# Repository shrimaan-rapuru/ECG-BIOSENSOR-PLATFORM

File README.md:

# Development and Evaluation of a Low-Cost Real-Time ECG Biosensing Platform

> Integrating Signal Processing, Robustness Analysis, and Physiological Visualization

**Shrimaan Rapuru** | The Early College at Guilford | Summer 2026
[Technical Report](report/) | [Results](results/) | [Dashboard](dashboard/)

---

## Abstract

This project investigates whether consumer-grade biosensing hardware can produce
physiologically meaningful cardiac metrics through optimized signal processing,
motivated by observed healthcare access inequality at Open Door Ministries, a
homeless shelter where I volunteer. Using a SparkFun AD8232 ECG module and Arduino
Uno R4 Minima ($102 total), I designed and validated a complete real-time ECG
acquisition and analysis pipeline. A 4th-order Butterworth bandpass filter
(0.5-40Hz) with IIR notch (60Hz) achieved visible PQRST morphology and 96.3%
mean R-peak detection accuracy across five validated resting trials. Three
structured experiments evaluated physiological response (resting vs. exercise vs.
recovery), electrode placement robustness, and comparative filter algorithm
performance. A key finding: Moving Average filtering achieves higher SNR but lower
detection reliability than Butterworth filtering, revealing that SNR alone is
insufficient to evaluate ECG filter quality. Results suggest low-cost ECG
acquisition is viable with careful signal processing methodology.

---

## Hero Figure

*Real-time ECG signal captured at 533Hz. All 5 PQRST waves clearly identified.
BPM: 89.5 | SDNN: 17.63ms | RMSSD: 23.65ms | 42 peaks detected.*

---

## Why This Matters

Standard clinical ECG systems cost $1,000-$10,000, placing cardiac monitoring
out of reach for many individuals and resource-limited settings. This project
asks a practical engineering question: can a $102 consumer-grade system produce
physiologically meaningful cardiac metrics with careful signal processing?

The answer, supported by validated experiments, is yes. This work demonstrates
that accessibility and rigor are not mutually exclusive. The same engineering
discipline that produces expensive medical devices can be applied to low-cost
hardware to yield credible, reproducible physiological measurements.

This project was motivated by direct observation of healthcare access inequality
at Open Door Ministries, where I coordinate volunteer scheduling. Every system
I build asks the same question I first asked there: how do we build tools that
actually reach the people who need them most?

---

## Key Results

- 96.3% mean R-peak detection accuracy across 5 validated resting trials
- 20% post-exercise BPM elevation (90 to 108 BPM) with parasympathetic rebound confirmed
- All 5 PQRST waves visible: Q-wave 7.9% of R, S-wave 28.0% of R
- Single electrode displacement (+-2cm) has minimal BPM impact; combined displacement degrades accuracy 6.3%
- Moving Average achieves higher SNR but lower detection reliability than Butterworth -- confirming SNR alone is insufficient to evaluate ECG filter quality

---

## System Architecture

| Layer | Components |
|---|---|
| Hardware | AD8232 AFE -> Arduino R4 Minima (14-bit ADC, 533Hz) -> USB Serial |
| Signal Processing | Butterworth Bandpass (0.5-40Hz) + IIR Notch (60Hz) + Peak Detection |
| Analysis | BPM calculation, HRV (SDNN/RMSSD), PQRST morphology |
| Visualization | Streamlit live dashboard + Matplotlib experimental plots |

---

## Hardware

### Bill of Materials

| Component | Part Number | Cost | Purpose |
|---|---|---|---|
| SparkFun AD8232 | SEN-12650 | $24.41 | ECG analog front-end |
| Electrode Cable | CAB-12970 | $9.60 | 3-lead electrode connection |
| Arduino Uno R4 Minima | -- | $19.99 | 14-bit ADC + USB serial |
| Ag/AgCl Electrodes 100pk | Kendall | $15.30 | Skin contact |
| Breadboard + jumpers | -- | $8.99 | Prototyping |
| Alcohol prep pads | -- | $7.00 | Skin preparation |
| Header pins | HiLetgo 40-pin | $5.49 | AD8232 connection |
| **Total** | | **$90.78** | |

### Wiring

| AD8232 Pin | Arduino Pin | Function |
|---|---|---|
| 3.3V | 3.3V | Power |
| GND | GND | Ground |
| OUTPUT | A0 | ECG signal |
| LO+ | D10 | Lead-off detect + |
| LO- | D11 | Lead-off detect - |

### Hardware Photos

| | |
|---|---|
|  |  |
| Hardware setup — AD8232 + Arduino R4 Minima | Electrode placement on subject |
|  |  |
| Apple Watch BPM validation — simultaneous recording | Full system setup overview |
### Electrode Placement
- **Red** -> Right chest (below collarbone)
- **Blue** -> Left chest (below collarbone)
- **Black** -> Right lower abdomen (ground)

### PCB Design
Custom PCB designed in EasyEDA featuring AD8232, decoupling capacitors (2x100nF,
1x10uF), bias resistors (2x10kOhm), 3.5mm PJ-320A electrode jack, and Arduino
pin headers. All components selected from JLCPCB assembly library.
Fabrication via JLCPCB planned as Phase 2.

---

## Signal Processing Pipeline

### Filter Specifications

| Filter | Type | Cutoff | Order | Purpose |
|---|---|---|---|---|
| High-pass | Butterworth | 0.5 Hz | 4 | Baseline drift removal |
| Low-pass | Butterworth | 40 Hz | 4 | EMG artifact removal |
| Notch | IIR | 60 Hz | Q=30 | Powerline interference |

**Implementation:** Zero-phase filtering (scipy filtfilt) eliminates phase
distortion for accurate RR interval timing. Critical for HRV analysis where
millisecond-level timing precision determines metric validity.

**Design decision:** The 0.5 Hz lower cutoff was deliberately calibrated to
preserve the low-amplitude P-wave rather than aggressively filtering baseline
drift -- prioritizing physiological completeness over visual cleanliness.

### Sampling Architecture

| Parameter | Value |
|---|---|
| Sampling frequency | 533.3 Hz (validated -- not assumed) |
| ADC resolution | 14-bit |
| Serial baud rate | 115200 bps |
| Timing jitter | 3.61ms |
| Recording duration | 30 seconds (16,000 samples) |
| Signal inversion | Applied (electrode polarity correction) |

### Peak Detection

Adaptive threshold: median + 0.5 x std
Minimum R-R distance: 0.6 x fs (prevents double detection)
Mean accuracy: 96.3% (range: 89.4%-100.0%, N=5 trials)

### Key Signal Processing Insight

A critical finding from Experiment 3: Moving Average filtering achieved higher
mean SNR (0.63 +/- 1.99 dB) compared to Butterworth bandpass (-10.14 +/- 3.58 dB),
yet demonstrated inferior BPM consistency across trials.

This reveals a fundamental limitation of SNR as an ECG filter evaluation metric:
- Moving Average smooths broadband noise but distorts QRS morphology
- Butterworth bandpass selectively removes non-physiological frequency content
- Visually cleaner signals are not necessarily physiologically superior
- Morphology preservation matters more than signal power ratio for reliable detection

### PQRST Morphology

| Wave | Amplitude | % of R | Physiological Meaning |
|---|---|---|---|
| P | visible | -- | Atrial depolarization |
| Q | -18.0 ADC | 7.9% | Septal depolarization |
| R | 228.3 ADC | 100% | Ventricular depolarization |
| S | -64.0 ADC | 28.0% | Late ventricular depolarization |
| T | ~50 ADC | ~22% | Ventricular repolarization |

---

## Experiments

### Experiment 1 -- Resting vs Exercise vs Recovery

| State | BPM | SDNN | RMSSD |
|---|---|---|---|
| Resting avg | 91.0 | 41.31ms | 45.93ms |
| Pre-exercise | 90 | -- | -- |
| Post-exercise | 108 | -- | -- |
| Recovery 1 | 86.7 | 54.33ms | 45.45ms |
| Recovery 2 | 92.1 | 20.18ms | 9.91ms |
| Recovery 3 | 95.7 | 9.24ms | 9.42ms |

### Experiment 2 -- Electrode Placement Robustness

| Condition | Avg BPM | vs Standard |
|---|---|---|
| Standard | 82.2 | baseline |
| RA off 2cm | 81.6 | -0.7% |
| LA off 2cm | 83.0 | +1.0% |
| Both off 2cm | 87.4 | +6.3% |

### Experiment 3 -- Filter Algorithm Comparison

| Algorithm | SNR | BPM | Time |
|---|---|---|---|
| Moving Average | 0.63 +/- 1.99 dB | 88.02 +/- 8.08 | 0.69ms |
| Butterworth | -10.14 +/- 3.58 dB | 80.14 +/- 22.04 | 4.4ms |
| Butterworth+Notch | -10.16 +/- 3.58 dB | 79.7 +/- 22.92 | 2.11ms |

---

## Live Dashboard

**Features:**
- Real-time ECG waveform with R-peak markers
- Live BPM display (color-coded red if >100 BPM)
- SDNN and RMSSD updating in real time
- Raw vs filtered signal toggle
- Lead-off detection alert
- CSV export for offline analysis

**Run locally:**

```
cd dashboard
pip install -r requirements.txt
streamlit run ecg_dashboard.py
```

> Not a medical device. For educational and research purposes only.

---

## Installation

```
pip install streamlit pandas numpy scipy pyserial plotly matplotlib
```

Arduino setup: Install Arduino IDE 2.x, select Arduino UNO R4 Minima,
set baud rate 115200, close Serial Monitor before running Python scripts.

---

## Repository Structure

```
ecg-biosensor/
├── signal_processing/           # Python analysis scripts
│   ├── serial_reader.py         # Arduino serial data capture
│   ├── filters.py               # Butterworth + notch filter pipeline
│   ├── peak_detection.py        # R-peak detection + HRV analysis
│   ├── pqrst_analysis.py        # PQRST wave visualization
│   ├── raw_vs_filtered.py       # Normalized comparison plots
│   ├── negative_deflection.py   # Q/S wave investigation
│   ├── filter_visual_comparison.py  # 4-panel algorithm comparison
│   ├── experiment_3.py          # Algorithm benchmarking
│   ├── quick_bpm_check.py       # 10-second live BPM check
│   └── validation.py            # Peak accuracy validation
├── dashboard/                   # Streamlit live dashboard
│   ├── ecg_dashboard.py
│   └── requirements.txt
├── results/                     # All experimental data and plots
│   ├── experiment_1/            # Resting/exercise/recovery (10 trials)
│   ├── experiment_2/            # Electrode placement (12 trials)
│   └── experiment_3/            # Filter comparison (15 trials)
├── hardware/                    # PCB design and documentation
│   ├── ecg_schematic.png
│   ├── block_diagram.png
│   └── dashboard_screenshots/
└── report/                      # Technical report and references
    └── references/              # 5 peer-reviewed papers
```

---

## Limitations

- **Single subject:** All data from one subject -- findings cannot be generalized
- **Short HRV windows:** 30-second recordings below the 5-minute clinical standard
- **Motion artifact:** Post-exercise filtered-pipeline recordings were unreliable
- **SNR methodology:** Standard SNR penalizes DC attenuation -- may not reflect morphology quality
- **Breadboard connections:** Mechanical instability motivates PCB fabrication

---

## Future Work

- [ ] Custom PCB fabrication via JLCPCB (schematic complete)
- [ ] Multi-subject validation study (N>=10)
- [ ] Streamlit Cloud deployment
- [ ] 5-minute HRV recording windows
- [ ] lfilter for real-time causal filtering
- [ ] Bland-Altman analysis vs commercial pulse oximeter
- [ ] Journal of Student Research submission (August 2026)

---

## References

1. Pan, J. & Tompkins, W.J. (1985). A real-time QRS detection algorithm. IEEE Trans Biomed Eng, 32(3), 230-236.
2. Task Force of ESC & NASPE (1996). Heart rate variability standards. Circulation, 93(5), 1043-1065.
3. Serhani, M.A. et al. (2020). ECG monitoring systems review. Sensors, 20(6), 1796.
4. Kohler, B.U. et al. (2002). Software QRS detection principles. IEEE Eng Med Biol, 21(1), 42-57.
5. Christov, I.I. (2004). Real time QRS detection adaptive threshold. BioMed Eng OnLine, 3(1), 28.

---

## License

MIT License -- see LICENSE for details.

---

## About

This project was motivated by observations at Open Door Ministries, a homeless
shelter where I volunteer as scheduling coordinator. Witnessing healthcare access
inequality firsthand raised a question that drove this research: can low-cost
consumer hardware produce clinically meaningful cardiac metrics with careful
signal processing? The answer, supported by validated experiments, is yes.

> "Every project I pursue asks the same question I first asked at Open Door:
> how do we build systems that actually reach the people who need them most?"

Shrimaan Rapuru | The Early College at Guilford, NC

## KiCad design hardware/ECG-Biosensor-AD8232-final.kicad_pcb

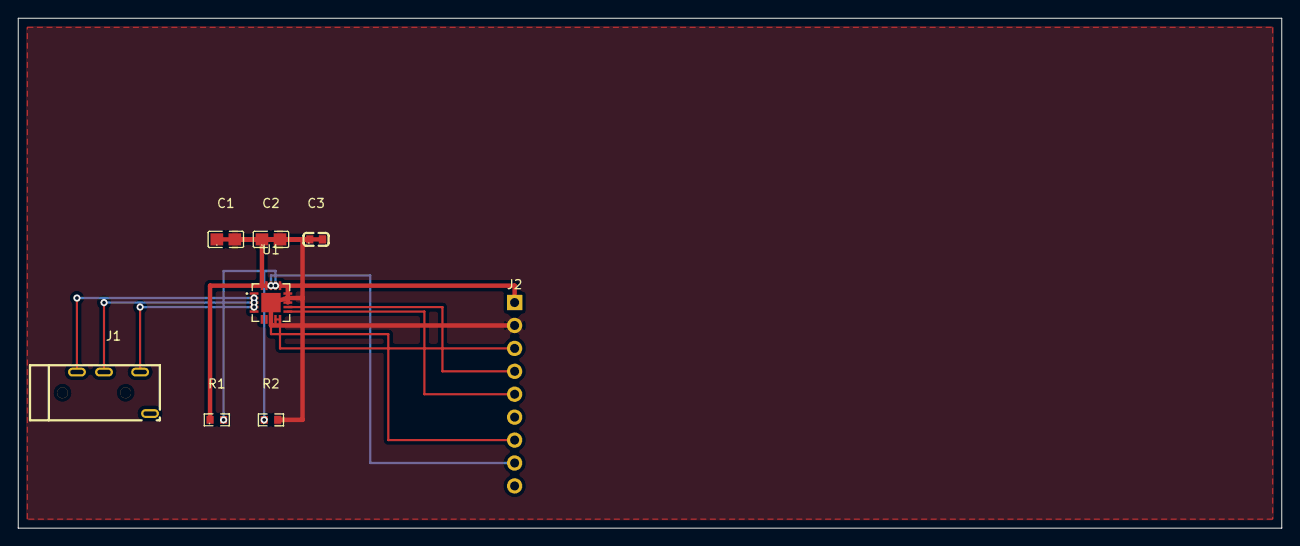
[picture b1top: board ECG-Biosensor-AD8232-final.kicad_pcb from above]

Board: 2 copper layers, 140.0 x 56.5 mm, 8 parts (0 on the bottom side), 11 nets.

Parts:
C1, C2: 100nF; C0805
C3: 10uF; C0603
J1: PJ-320A; AUDIO-TH_PJ-320A_C49284721
J2: OUTPUT_HDR; HDR-TH_9P-P2.54-V
R1, R2: 10k; R0603
U1: AD8232ACPZ-R7; LFCSP-20_L4.0-W4.0-P0.50-TL-EP2.7

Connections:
ECG_INN: J1.3, U1.3
ECG_INP: J1.5, U1.2
ECG_OUT: J2.3, U1.10
GND: C1.2, C2.2, C3.2, J2.2, R2.2, U1.14, U1.21
IAOUT: J2.8, U1.18
LO_MINUS: J2.5, U1.11
LO_PLUS: J2.4, U1.12
REFIN: R1.2, R2.1, U1.17
REFOUT: J2.7, U1.8
RLD: J1.4, U1.4, U1.5
VCC: C1.1, C2.1, C3.1, J2.1, J2.6, R1.1, U1.13, U1.16, U1.20

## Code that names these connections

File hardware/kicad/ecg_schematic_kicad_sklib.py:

from collections import defaultdict
from skidl import Pin, Part, Alias, SchLib, SKIDL, TEMPLATE

from skidl.pin import pin_types

SKIDL_lib_version = '0.0.1'

ecg_schematic_kicad = SchLib(tool=SKIDL).add_parts(*[
        Part(**{ 'name':'C', 'dest':TEMPLATE, 'tool':SKIDL, 'aliases':Alias({'C'}), 'ref_prefix':'C', 'fplist':None, 'footprint':'ecg_kicad:C0805', 'keywords':None, 'description':'', 'datasheet':None, 'pins':[
            Pin(num='1',name='P',func=pin_types.PASSIVE),
            Pin(num='2',name='N',func=pin_types.PASSIVE)] }),
        Part(**{ 'name':'R', 'dest':TEMPLATE, 'tool':SKIDL, 'aliases':Alias({'R'}), 'ref_prefix':'R', 'fplist':None, 'footprint':'ecg_kicad:R0603', 'keywords':None, 'description':'', 'datasheet':None, 'pins':[
            Pin(num='1',name='P',func=pin_types.PASSIVE),
            Pin(num='2',name='N',func=pin_types.PASSIVE)] }),
        Part(**{ 'name':'PJ320A', 'dest':TEMPLATE, 'tool':SKIDL, 'aliases':Alias({'PJ320A'}), 'ref_prefix':'J', 'fplist':None, 'footprint':'ecg_kicad:AUDIO-TH_PJ-320A_C49284721', 'keywords':None, 'description':'', 'datasheet':None, 'pins':[
            Pin(num='1',name='T',func=pin_types.PASSIVE),
            Pin(num='2',name='R1',func=pin_types.PASSIVE),
            Pin(num='3',name='S',func=pin_types.PASSIVE)] }),
        Part(**{ 'name':'Conn1x9', 'dest':TEMPLATE, 'tool':SKIDL, 'aliases':Alias({'Conn1x9'}), 'ref_prefix':'J', 'fplist':None, 'footprint':'ecg_kicad:HDR-TH_40P-P2.54-V-M-1', 'keywords':None, 'description':'', 'datasheet':None, 'pins':[
            Pin(num='1',name='P1',func=pin_types.PASSIVE),
            Pin(num='2',name='P2',func=pin_types.PASSIVE),
            Pin(num='3',name='P3',func=pin_types.PASSIVE),
            Pin(num='4',name='P4',func=pin_types.PASSIVE),
            Pin(num='5',name='P5',func=pin_types.PASSIVE),
            Pin(num='6',name='P6',func=pin_types.PASSIVE),
            Pin(num='7',name='P7',func=pin_types.PASSIVE),
            Pin(num='8',name='P8',func=pin_types.PASSIVE),
            Pin(num='9',name='P9',func=pin_types.PASSIVE)] }),
        Part(**{ 'name':'AD8232ACPZ-R7', 'dest':TEMPLATE, 'tool':SKIDL, 'aliases':Alias({'AD8232ACPZ-R7'}), 'ref_prefix':'U', 'fplist':None, 'footprint':'ecg_kicad:LFCSP-20_L4.0-W4.0-P0.50-TL-EP2.7', 'keywords':None, 'description':'', 'datasheet':None, 'pins':[
            Pin(num='1',name='HPDRIVE',func=pin_types.BIDIR),
            Pin(num='2',name='+IN',func=pin_types.INPUT),
            Pin(num='3',name='-IN',func=pin_types.INPUT),
            Pin(num='4',name='RLDFB',func=pin_types.INPUT),
            Pin(num='5',name='RLD',func=pin_types.OUTPUT),
            Pin(num='6',name='SW',func=pin_types.BIDIR),
            Pin(num='7',name='OPAMP+',func=pin_types.INPUT),
            Pin(num='8',name='REFOUT',func=pin_types.OUTPUT),
            Pin(num='9',name='OPAMP-',func=pin_types.INPUT),
            Pin(num='10',name='OUT',func=pin_types.OUTPUT),
            Pin(num='11',name='LOD-',func=pin_types.OUTPUT),
            Pin(num='12',name='LOD+',func=pin_types.OUTPUT),
            Pin(num='13',name='SDN#',func=pin_types.INPUT),
            Pin(num='14',name='AC/DC#',func=pin_types.INPUT),
            Pin(num='15',name='FR',func=pin_types.INPUT),
            Pin(num='16',name='+VS',func=pin_types.PWRIN),
            Pin(num='17',name='REFIN',func=pin_types.INPUT),
            Pin(num='18',name='IAOUT',func=pin_types.OUTPUT),
            Pin(num='19',name='HPSENSE',func=pin_types.INPUT),
            Pin(num='20',name='EP',func=pin_types.PWRIN),
            Pin(num='21',name='GND',func=pin_types.PWRIN)] })])

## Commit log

2026-05-16 Week 1-2: Hardware working, filters, peak detection complete
2026-05-16 Initialize README with project details
    Added project overview, results, hardware, features, and status.
2026-05-17 Week 2: sampling rate validated 533Hz, fs updated, quick BPM check added
2026-05-17 Add related work section to README
2026-05-17 Update related work references in README
2026-05-17 Add reference PDFs for technical report
2026-05-19 Update ECG signal acquisition rate to 533Hz
    Updated ECG signal acquisition rate from 500Hz to 533Hz and validated the change.
2026-05-19 Include hardware setup and electrode placement images
    Add hardware setup images to README
2026-05-19 Revise README with project overview and updates
    Updated project details, added abstract and system architecture sections, and revised status information.
2026-05-19 Refine README formatting and project description
    Updated the README to improve clarity and formatting, including changes to the project description and repository link.
2026-05-20 Add requirements.txt and hardware photos
2026-05-23 Add resting trials 1-5 Subject 2 with header pins
2026-05-23 Add clean ECG filtered peaks plot for website
2026-05-23 Add PQRST wave analysis plot — all 5 waves visible
2026-05-23 Add publication-quality PQRST plot with validation table
2026-05-24 Add recovery trials 1-3 and complete exercise experiment data
2026-05-24 Final corrected exercise trial data — pre 90 post 108
2026-05-25 Add peak accuracy validation — 96.3% mean accuracy
2026-05-25 Add negative deflection investigation and normalized signal plots
2026-05-25 Add Streamlit ECG dashboard
2026-05-27 Complete Experiment 2 — electrode placement study all 4 conditions
2026-05-27 Complete Experiment 3 — filter algorithm comparison
2026-05-28 Add live dashboard screenshots and complete session documentation
2026-05-29 Add PCB schematic and layout — EasyEDA design v1.0
2026-05-29 Add system block diagram and PCB design documentation
2026-05-29 Complete GitHub README — full project documentation
2026-05-29 Fix dashboard screenshot extension
2026-05-29 Add firmware, docs, experiments folders — improve repo structure
2026-05-29 Add README files to firmware, docs, experiments folders
2026-06-03 Fix subject photo file extensions
2026-06-03 Rename validation video
2026-06-03 Add hardware photos to README
2026-06-03 Add Bland-Altman validation plot vs Apple Watch Series 8
2026-06-03 Add Bland-Altman validation plot — ECG vs Apple Watch
2026-06-06 Add Subject 5 Apple Watch validation data
2026-06-06 Update Bland-Altman plot — N=10 combined Subjects 4 and 5
2026-06-06 Add Subject 5 PQRST analysis plot
2026-06-06 Add Subject 5 PQRST analysis, update validation plot with r and MAPE
2026-06-07 Add Subject 2 Apple Watch validation — N=15 combined Bland-Altman
2026-06-07 Add Subject 2 photos, updated plots, Subject 6 trial 1
2026-06-08 Add CSV playback demo dashboard for Streamlit Cloud
2026-06-08 Fix requirements.txt for Streamlit Cloud
2026-06-08 Add scipy to requirements
2026-06-09 Add KiCad PCB layout screenshot
2026-06-09 Add KiCad PCB project — Python-generated netlist, component placement, board outline
2026-06-12 Add Python version to runtime.txt
2026-06-12 Specify Python version requirement in pyproject.toml
2026-06-12 Fix URL in load_ecg_data function and clean up code
2026-06-12 Update requirements.txt to remove version constraints
    Removed specific versioning for several packages.
2026-06-12 Specify package versions in requirements.txt
2026-06-12 Fix requirements.txt, add final PCB files and gerbers
2026-06-12 Fix scipy version to 1.13.1
2026-06-12 Add streamlit version to requirements.txt
2026-06-12 Fix Streamlit dependencies
2026-06-12 Revert requirements to stable Python 3.11 versions
2026-06-12 Fix URL for loading ECG data
2026-06-12 Remove CSV loading messages from ecg_dashboard_demo
    Removed CSV loading messages from the dashboard.
2026-06-12 Refactor ECG dashboard for static waveform display
    Removed playback controls and added static waveform display.
2026-06-12 Fix timestamp calculation for ECG data
